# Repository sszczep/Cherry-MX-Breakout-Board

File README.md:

# Cherry MX Breakout Boards 

<table>
 <tbody>
  <tr>
   <td></td>
   <td>
    
Two breakout boards designed in **KiCad**. 

Both feature reverse-mounted addressable RGB LED **LTST-A683CEGBW**. 

Both are hot-swap capable (**Kailh Socket** / **Mill-Max 7305**).

Total board dimensions: **26 x 19 mm**.
   </td>
  </tr>
 </tbody>
</table>

**Mill-Max 7305 holes are compatible with standalone switches so they can be soldered directly to the board.**

| Schematic | PCB (Kailh Socket) | PCB (Mill-Max 7305) |
|---|---|---|
|  |  |  |

## Kailh Socket Renders

| Top View | Bottom View |
|---|---|
|  |  |

> Kailh Socket 3D Model was obtained from [*QMK*](https://github.com/qmk). All credits go to them. The exact file can be found [here](https://github.com/qmk/qmk_hardware/blob/master/components/kailh_socket_mx.stp).

## Mill-Max 7305 Renders

| Top View | Bottom View |
|---|---|
|  |  |

## Real Photos
<table>
 <tbody>
  <tr>
   <td colspan="3"></td>
  </tr>
  <tr>
   <td></td>
   <td></td>
   <td></td>
  </tr>
  <tr>
   <td></td>
   <td></td>
   <td></td>
  </tr>
 </tbody>
</table>

## Hooking up with Arduino
<table>
 <thead>
  <tr>
   <th>Code</th>
   <th>Wiring diagram</th>
  </tr>
 </thead>
 <tbody>
  <tr>
   <td><pre lang="cpp">
#include "FastLED.h"

    const int ledPin = 6;
    const int buttonPin = 7;

    int ledHue = 0;
    const int ledSaturation = 255;
    const int ledBrightness = 255;

    CRGB leds[1];

    void setup() {
      pinMode(buttonPin, INPUT_PULLUP);
      FastLED.addLeds<WS2811, ledPin>(leds, 1);
    }

    void loop() {
      if(digitalRead(buttonPin) == LOW) ledHue++;

      leds[0].setHSV(ledHue, ledSaturation, ledBrightness);
      FastLED.show();
    }
   </pre></td>
   <td></td>
  </tr>
 </tbody>
</table>

## What socket is right for me?
<table>
 <thead>
  <tr>
   <td></td>
   <td>Kailh Socket</td>
   <td>Mill-Max 7305 & 0305</td>
  </tr>
 </thead>
 <tbody>
  <tr>
   <td>Cost per switch</td>
   <td>$0.10 on <a href="https://kbdfans.com/products/mechanical-keyboard-switches-kailh-pcb-socket">kbdfans.com</a></td>
   <td>about $0.88 on <a href="https://www.digikey.com/product-detail/en/mill-max-manufacturing-corp/7305-0-15-15-47-27-10-0/ED1039-ND/1765737">digikey.com</a></td>
  </tr>
  <tr>
   <td>Requires compatible PCB?</td>
   <td>Yes</td>
   <td>No</td>
  </tr>
  <tr>
   <td>Soldering difficulty</td>
   <td colspan="2">Both socket types are easy to solder and there shouldn't be any problems</td>
  </tr>
  <tr>
   <td>General Notes</td>
   <td colspan="2">Kailh Sockets are much cheaper when it comes to custom builds but require custom PCB. Mill-Max connectors are not as stabilized as they make an extra gap between PCB and switch. Mill-Max 7305 is preferable over 0305, it's thinner so the gap is not that wide. Swapping switches seems easier using Kailh Sockets, Mill-Max connectors tend to bend sockets' pins. In my opinion, Mill-Max connectors should be taken into an account only when you modify pre-existing PCB as they have no advantage over Kailh Sockets and simply cost more
  </tr>
 </tbody>
</table>

## Datasheets

  * [Cherry MX](https://github.com/sszczep/Cherry-MX-Breakout-Board/blob/master/datasheets/Cherry%20MX.pdf)
  * [LTST-A683CEGBW](https://github.com/sszczep/Cherry-MX-Breakout-Board/blob/master/datasheets/LTST-A683CEGBW.pdf)
  * [Kailh Socket](https://github.com/sszczep/Cherry-MX-Breakout-Board/blob/master/datasheets/Kailh%20Socket.pdf)
  * [Mill-Max](https://github.com/sszczep/Cherry-MX-Breakout-Board/blob/master/datasheets/Mill-Max.pdf)

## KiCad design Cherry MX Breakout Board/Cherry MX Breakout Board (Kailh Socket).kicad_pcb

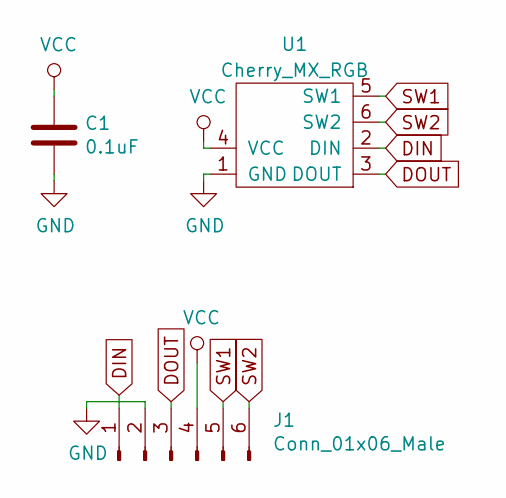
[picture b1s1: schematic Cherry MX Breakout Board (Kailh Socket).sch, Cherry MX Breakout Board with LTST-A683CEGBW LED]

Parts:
C1: 0.1uF; C_0603_1608Metric
J1: Conn_01x06_Male; PinHeader_1x06_P2.54mm_Vertical
U1: Cherry_MX_RGB; Cherry-MX_Plate-Mounted_LTST-A683CEGBW_Kailh_Socket

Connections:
DIN: J1.1, U1.2 (DIN)
DOUT: J1.3, U1.3 (DOUT)
GND: C1.2, J1.2, U1.1 (GND)
SW1: J1.5, U1.5 (SW1)
SW2: J1.6, U1.6 (SW2)
VCC: C1.1, J1.4, U1.4 (VCC)

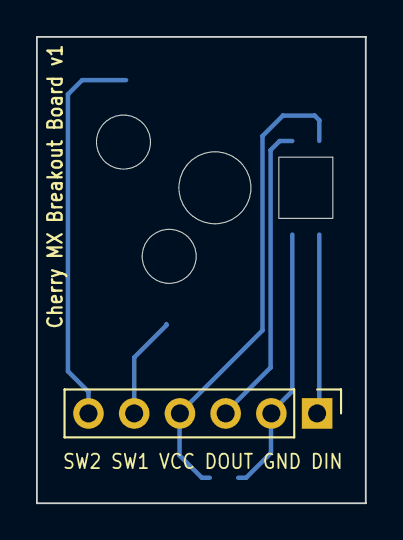
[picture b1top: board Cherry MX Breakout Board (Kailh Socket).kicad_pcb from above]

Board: 2 copper layers, 18.3 x 25.9 mm, 3 parts (1 on the bottom side), 6 nets.

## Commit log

2020-01-23 Rename files
2020-01-23 Add datasheets
2020-01-23 Update project files, add gerbers
2020-01-26 Fix footprints and PCBs
    - removed silkscreen of Cherry MX and Kailh Socket
    - LTST-A683CEGBW pinout and model was rotated which caused invalid connections
2020-03-27 Downscale and rename photos
2020-03-27 Upload gif
2020-03-29 Fix Arduino code
2020-04-01 Add PCB Mounted footprints
2020-04-06 Move media to seperate branch
2020-04-06 Add media

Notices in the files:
Cherry MX Breakout Board/Cherry MX Breakout Board (Kailh Socket).kicad_pcb:
License: MIT
